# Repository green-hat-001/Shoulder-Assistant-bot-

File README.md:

# Companion Spider Bot

## Overview
This is a fully custom, 12-DOF quadruped companion robot. This was made to make school and general life a lot more fun and streamlined. This bot will connect to my NAS and be able to transcribe and capture relevant pictures during lectures to be reviewed later. It can also act as an auxiliary screen, and the reason I have made this into a bot is that I wanted to mimic Ankis Cosmo and have that sort of fun and quirky factor to this.

##  Key Features
* **12-DOF Quadrupedal Locomotion:** Powered by 12x MG90S metal gear micro servos, offering 3 degrees of freedom per leg for inverse kinematics-driven walking gaits.
* **Custom "Chip-Down" Mainboard:** A integrated custom PCB built around the ESP32-S3-WROOM-1 module, keeping the electronics profile incredibly thin.
* **Intelligent Power Delivery:** * Simultaneous charge-and-play capability via USB-C.
* **Computer Vision:** Integrated OV2640 camera module for AI-driven object recognition and tracking.

##  Hardware Bill of Materials (BOM)

### Electronics & Brain
* **Microcontroller:** ESP32-S3-WROOM-1 (Custom PCB)
* **Servo Controller:** PCA9685 16-Channel PWM Driver
* **Vision:** OV2640 Camera Module 
* **Custom PCB:** 2-layer custom board (SMT assembled)
* **Intelligent Power Delivery:** * Simultaneous charge-and-play capability via USB-C.
  * IP2326 Boost Module steps 5V up to 8.4V to charge the onboard 2S LiPo.
  * Onboard XL4015 buck converter drops battery voltage to a clean, high-current 5V for the servo array, while an AMS1117 handles 3.3V logic.
  * Schottky diode OR-gate ensures the ESP32-S3 remains safely powered via USB during programming, even when the battery is disconnected.

### Power System
* **Battery:** 2S LiPo (7.4V, 2000mAh, 20C) with XT30 connector
* **Charge Controller:** IP2326 2S Step-Up Module (Modified for raw pad soldering)
* **Voltage Regulation:** XL4015 (5V out for servos), AMS1117 (3.3V out for logic)
* **Smartwatch Integration:** Stripped Samsung Watch 7 charger + logic-level MOSFET

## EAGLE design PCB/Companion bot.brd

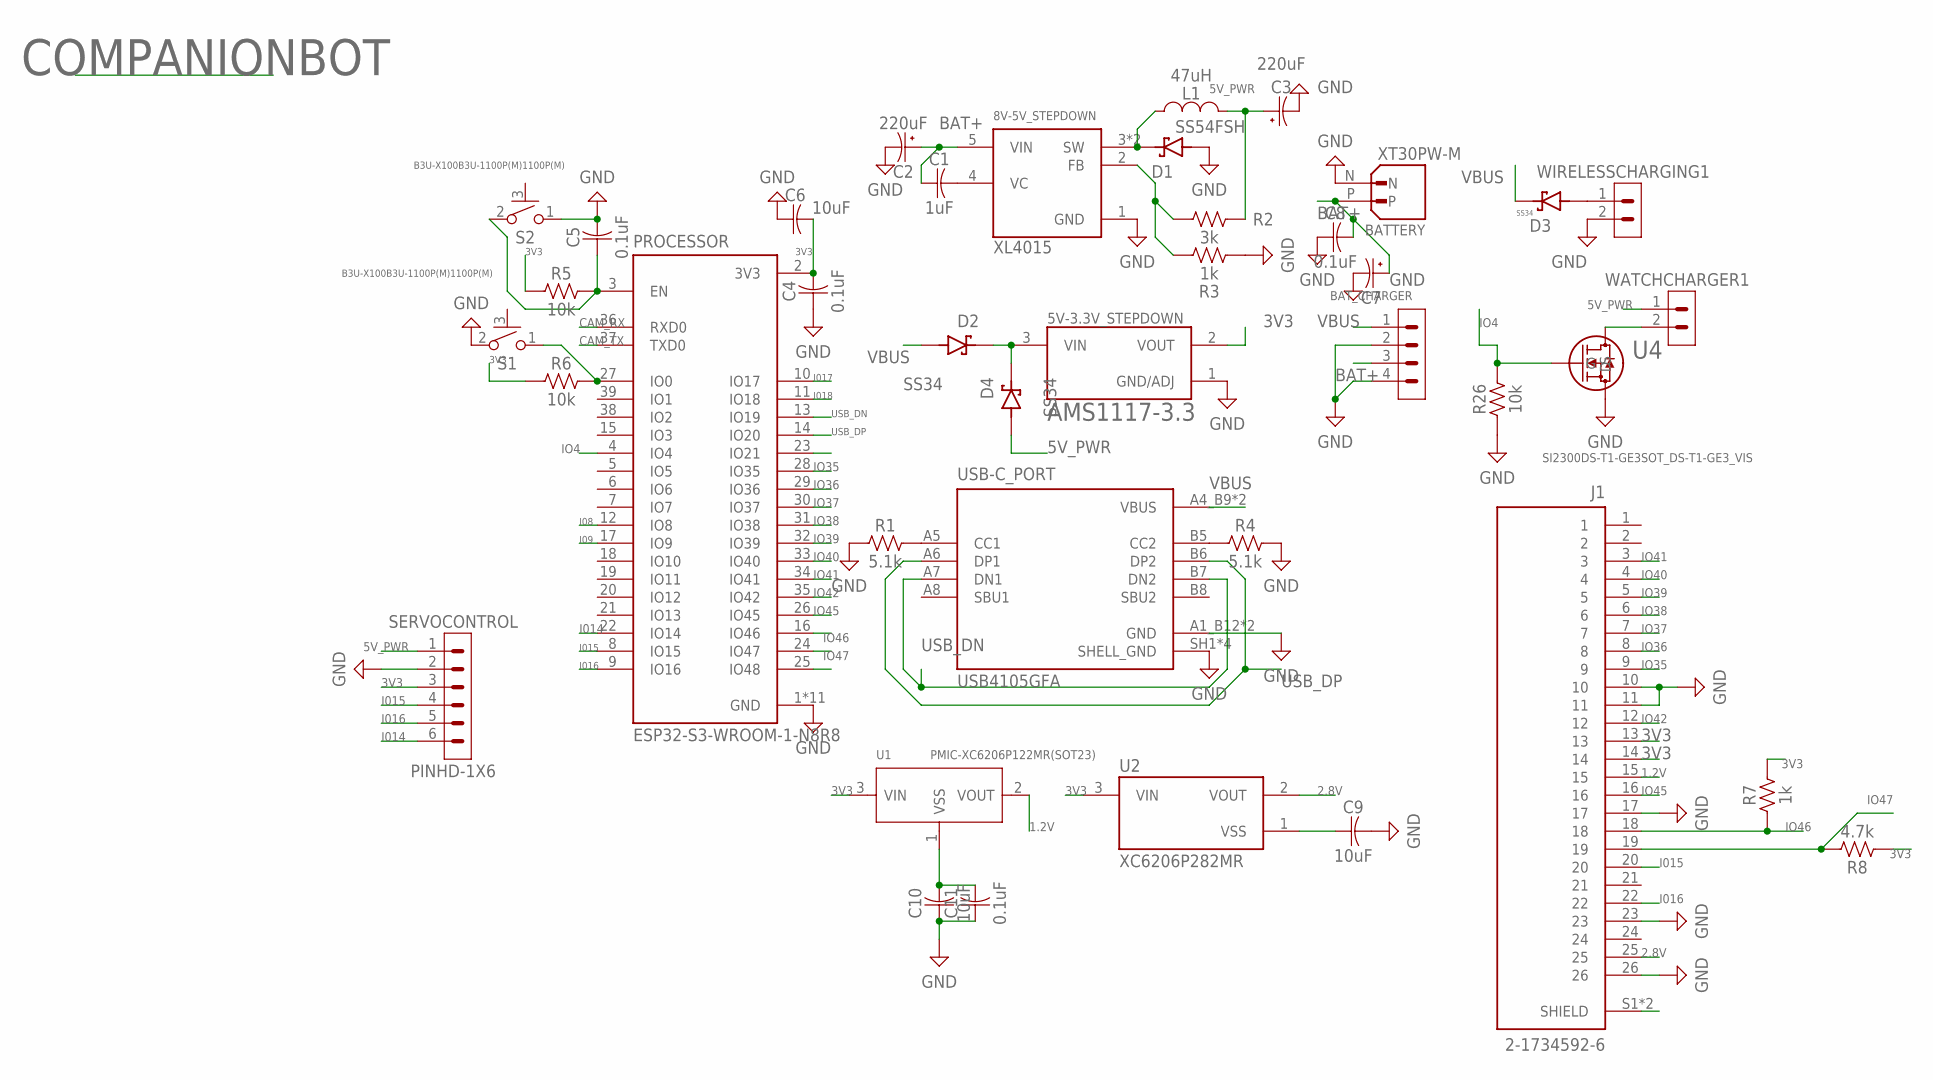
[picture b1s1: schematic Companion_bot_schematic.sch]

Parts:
5V-3.3V_STEPDOWN: AMS1117-3.3; SOT229P700X180-4N
8V-5V_STEPDOWN: XL4015; CONV_XL4015
BATTERY: XT30PW-M; AMASS_XT30PW-M
BAT_CHARGER: PINHD-1X4; 1X04
C1: 1uF; CAPC1005X60
C2, C3: 220uF; CAPMP3216X180N
C4, C5, C8, C11: 0.1uF; CAPC1005X60
C6, C9, C10: 10uF; CAPC1005X60
C7: C-POL-US_TANTALUM-1206(3216-METRIC); CAPMP3216X180N
D1: SS54FSH; SODFL4725X110N
D2, D3, D4: SS34; DIO_SS34
J1: 2-1734592-6; TE_2-1734592-6
L1: 47uH; INDC1006X60N
PROCESSOR: ESP32-S3-WROOM-1-N8R8; XCVR_ESP32S3WROOM1N8R8
R1, R4: 5.1k; RESC1005X40
R2: 3k; RESC1005X40
R3, R7: 1k; RESC1005X40
R5, R6, R26: 10k; RESC1005X40
R8: 4.7k; RESC1005X40
S1, S2: B3U-X100B3U-1100P(M)1100P(M); B3U-1100P(M)
SERVOCONTROL: PINHD-1X6; 1X06
U1: PMIC-XC6206P122MR(SOT23); SOT-23
U2: XC6206P282MR; VREG_XC6206P282MR
U4: SI2300DS-T1-GE3SOT_DS-T1-GE3_VIS; SOT_DS-T1-GE3_VIS
USB-C_PORT: USB4105GFA; GCT_USB4105GFA
WATCHCHARGER1: PINHD-1X2; 1X02
WIRELESSCHARGING1: PINHD-1X2; 1X02

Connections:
1.2V: J1.15, U1.2 (VOUT)
2.8V: J1.25, U2.2 (VOUT)
3V3: 5V-3.3V_STEPDOWN.2 (VOUT), C4.2, C6.2, J1.13, J1.14, PROCESSOR.2 (3V3), R5.1, R6.1, R7.2, R8.1, SERVOCONTROL.3, U1.3 (VIN), U2.3 (VIN)
5V_PWR: C3.1 (+), D4.A, L1.2, R2.2, SERVOCONTROL.1, WATCHCHARGER1.1
BAT+: 8V-5V_STEPDOWN.5 (VIN), BATTERY.P, BAT_CHARGER.3, C1.1, C2.1 (+), C7.1 (+), C8.2
CAM_RX: PROCESSOR.36 (RXD0)
CAM_TX: PROCESSOR.37 (TXD0)
GND: 5V-3.3V_STEPDOWN.1 (GND/ADJ), 8V-5V_STEPDOWN.1 (GND), BATTERY.N, BAT_CHARGER.2, BAT_CHARGER.4, C2.2 (-), C3.2 (-), C4.1, C5.2, C6.1, C7.2 (-), C8.1, C9.2, C10.1, C11.1, D1.A, J1.10, J1.11, J1.17, J1.23, J1.26, PROCESSOR.1 (GND), PROCESSOR.40 (GND), PROCESSOR.41_1 (GND), PROCESSOR.41_2 (GND), PROCESSOR.41_3 (GND), PROCESSOR.41_4 (GND), PROCESSOR.41_5 (GND), PROCESSOR.41_6 (GND), PROCESSOR.41_7 (GND), PROCESSOR.41_8 (GND), PROCESSOR.41_9 (GND), R1.1, R3.2, R4.2, R26.1, S1.2 (1), S2.1 (2), SERVOCONTROL.2, U4.3 (S), USB-C_PORT.A1_B12 (GND), USB-C_PORT.B1_A12 (GND), USB-C_PORT.SH1 (SHELL_GND), USB-C_PORT.SH2 (SHELL_GND), USB-C_PORT.SH3 (SHELL_GND), USB-C_PORT.SH4 (SHELL_GND), WIRELESSCHARGING1.2
I08: PROCESSOR.12 (IO8)
I09: PROCESSOR.17 (IO9)
I014: PROCESSOR.22 (IO14), SERVOCONTROL.6
I015: J1.20, PROCESSOR.8 (IO15), SERVOCONTROL.4
I016: J1.22, PROCESSOR.9 (IO16), SERVOCONTROL.5
I017: PROCESSOR.10 (IO17)
I018: PROCESSOR.11 (IO18)
IO4: PROCESSOR.4 (IO4), R26.2, U4.1 (G)
IO35: J1.9, PROCESSOR.28 (IO35)
IO36: J1.8, PROCESSOR.29 (IO36)
IO37: J1.7, PROCESSOR.30 (IO37)
IO38: J1.6, PROCESSOR.31 (IO38)
IO39: J1.5, PROCESSOR.32 (IO39)
IO40: J1.4, PROCESSOR.33 (IO40)
IO41: J1.3, PROCESSOR.34 (IO41)
IO42: J1.12, PROCESSOR.35 (IO42)
IO45: J1.16, PROCESSOR.26 (IO45)
IO46: J1.18, PROCESSOR.16 (IO46), R7.1
IO47: J1.19, PROCESSOR.24 (IO47), R8.2
unnamed: R1.2, USB-C_PORT.A5 (CC1)
unnamed: R4.1, USB-C_PORT.B5 (CC2)
unnamed: 8V-5V_STEPDOWN.4 (VC), C1.2
unnamed: 8V-5V_STEPDOWN.3 (SW), 8V-5V_STEPDOWN.3.1 (SW), D1.C (K), L1.1
unnamed: 8V-5V_STEPDOWN.2 (FB), R2.1, R3.1
unnamed: C5.1, PROCESSOR.3 (EN), R5.2, S2.2 (1)
unnamed: PROCESSOR.27 (IO0), R6.2, S1.1 (2)
unnamed: 5V-3.3V_STEPDOWN.3 (VIN), D2.C (K), D4.C (K)
unnamed: C9.1, U2.1 (VSS)
unnamed: U4.2 (D), WATCHCHARGER1.2
unnamed: D3.A, WIRELESSCHARGING1.1
unnamed: J1.S1 (SHIELD), J1.S2 (SHIELD)
USB_DN: PROCESSOR.13 (IO19), USB-C_PORT.A7 (DN1), USB-C_PORT.B7 (DN2)
USB_DP: PROCESSOR.14 (IO20), USB-C_PORT.A6 (DP1), USB-C_PORT.B6 (DP2)
VBUS: BAT_CHARGER.1, D2.A, D3.C (K), USB-C_PORT.A4_B9 (VBUS), USB-C_PORT.B4_A9 (VBUS)
VSS: C10.2, C11.2, U1.1 (VSS)

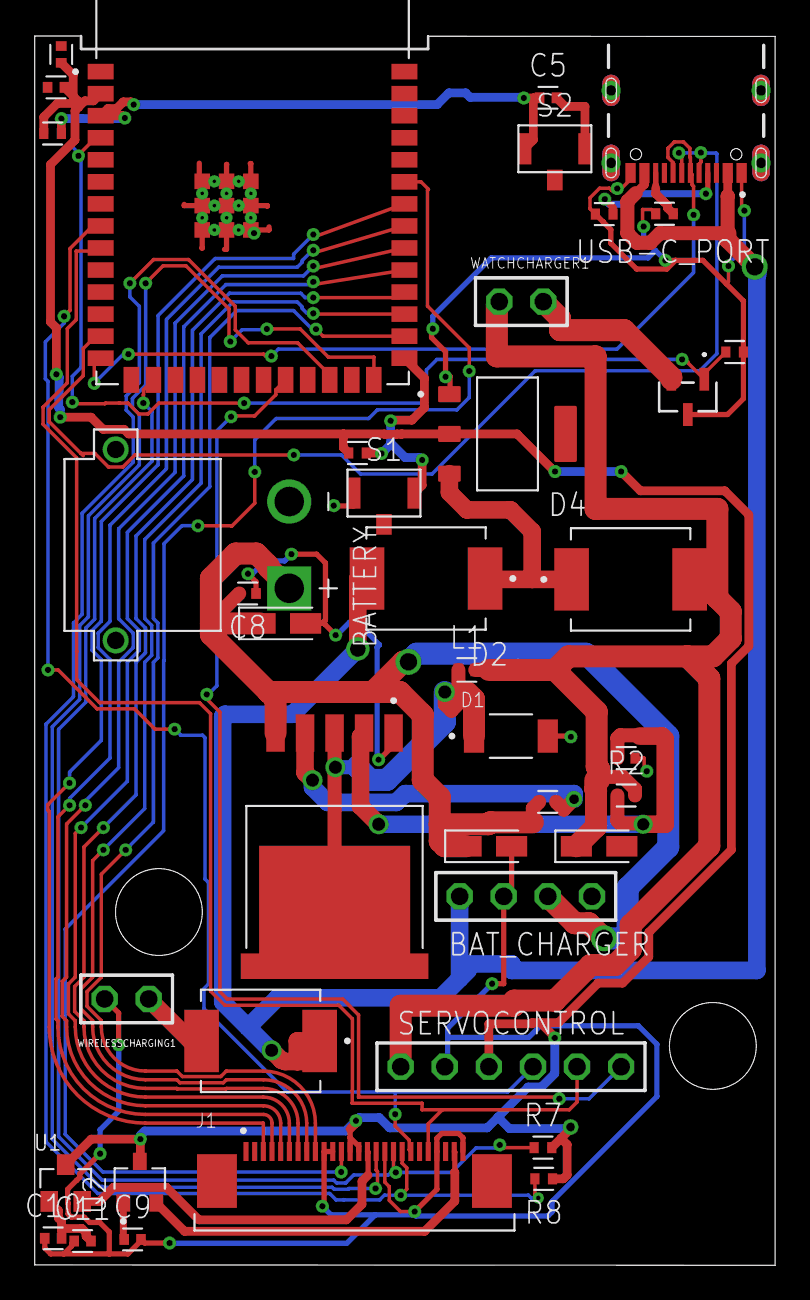
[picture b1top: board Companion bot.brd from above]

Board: 2 copper layers, 42.5 x 70.7 mm, 40 parts (0 on the bottom side), 37 nets.

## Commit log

2026-04-13 Upload
2026-04-13 Firmware
2026-04-13 Updtae readme
2026-04-13 Revise README for clarity and updates
    Updated project description and key features for clarity. Revised future roadmap and acknowledgments.
2026-04-13 Update README with image and project overview
    Added an image and expanded the overview of the Companion Spider Bot.
2026-04-15 Firmware and organisation
2026-05-07 Gerber files
2026-05-07 CAD design files

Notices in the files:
parts and their libraries:
2026-03-09_07-57-06_Library: COPYRIGHT: Copyright (C) 2026 Ultra Librarian. All rights reserved.
